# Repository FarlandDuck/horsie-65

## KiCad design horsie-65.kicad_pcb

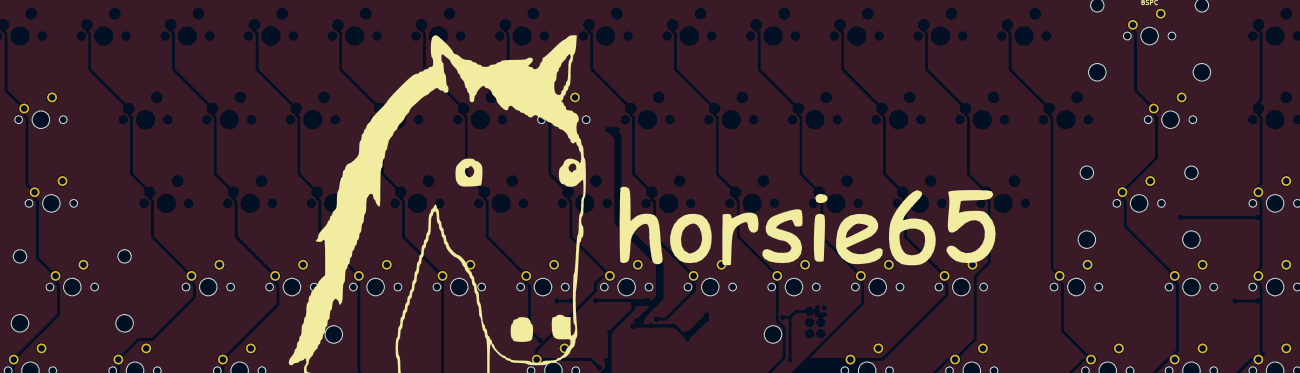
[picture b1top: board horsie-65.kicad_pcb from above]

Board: 2 copper layers, 31 parts (0 on the bottom side), 8 nets, no tracks yet.

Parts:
SW14: BSPC; MXOnly-2U-NoLED
SW16: TAB; MXOnly-1.5U-NoLED
SW22: Y; MXOnly-1U-NoLED
SW29: \|; MXOnly-1.5U-NoLED
SW31: CAPS; MXOnly-1.75U-NoLED
SW42: '; MXOnly-1U-NoLED
SW43: ENTR; MXOnly-2.25U-NoLED
SW44: PGUP; MXOnly-1U-NoLED
SW45: LSHF; MXOnly-2.25U-NoLED
SW46: Z; MXOnly-1U-NoLED
SW47: X; MXOnly-1U-NoLED
SW48: C; MXOnly-1U-NoLED
SW49: V; MXOnly-1U-NoLED
SW50: B; MXOnly-1U-NoLED
SW51: N; MXOnly-1U-NoLED
SW52: M; MXOnly-1U-NoLED
SW53: ,<; MXOnly-1U-NoLED
SW54: .>; MXOnly-1U-NoLED
SW55: /?; MXOnly-1U-NoLED
SW56: RSHF; MXOnly-1.75U-NoLED
SW57: UARW; MXOnly-1U-NoLED
SW58: PGDN; MXOnly-1U-NoLED
SW59: LCTR; MXOnly-1.25U-NoLED
SW60: WNDW; MXOnly-1.25U-NoLED
SW61: LALT; MXOnly-1.25U-NoLED
SW62: SPCB; MXOnly-6.25U-NoLED
SW63: RALT; MXOnly-1.25U-NoLED
SW64: FNKY; MXOnly-1.25U-NoLED
SW65: LARW; MXOnly-1U-NoLED
SW66: DARW; MXOnly-1U-NoLED
SW67: RARW; MXOnly-1U-NoLED

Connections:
col0: SW16.1, SW31.1, SW45.1, SW59.1
col1: SW46.1, SW60.1
col2: SW47.1, SW61.1
col6: SW22.1, SW51.1, SW62.1
col10: SW55.1, SW63.1
col12: SW56.1, SW65.1
col13: SW14.1, SW29.1, SW43.1, SW57.1, SW66.1
col14: SW44.1, SW58.1, SW67.1

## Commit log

2022-05-10 Added submodules
2022-05-11 Schema
2022-05-12 flipped switches
2022-05-12 more pcb
2022-05-12 more routing
2022-05-12 aesthetics 1
2022-05-12 pre ground fill
2022-05-12 isolate clock
2022-05-12 minor stuff
2022-05-12 ground fill fix
2022-05-12 bruhhh
2022-05-12 ground fill
2022-05-12 flip spcb
2022-05-12 minor fixes
2022-05-12 feedback fixes
2022-05-12 pre ground fill again
2022-05-12 ground fills
2022-05-12 logos
2022-05-12 sheeesh
2022-05-13 pre manu
2022-05-13 post purchase

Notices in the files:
horsie-65.kicad_pcb:
v1.0.0 - © Horsierer 2022
